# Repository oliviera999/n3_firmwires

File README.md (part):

# Firmwires – Projets ESP32 et Arduino (PlatformIO)

*Contexte : [salle aérée n³](https://n3.olution.info) · Données : [iot.olution.info](https://iot.olution.info). Voir [README racine](../README.md), [RECOMMANDATIONS_IOT](../RECOMMANDATIONS_IOT.md), [inventaire des appareils](../docs/inventaire_appareils.md).*

Dépôt regroupant **plusieurs firmwares** : deux projets principaux ESP32 (serre/aquaponie, station météo), trois projets ESP32-CAM d’envoi de photos vers un serveur web, et le kit **ratata** (ZYC0108-EN) avec exemples Arduino UNO et ESP32-CAM. Chaque projet (ou environnement) est compilable avec **PlatformIO**.

## Projets

| Projet | Dossier | Carte | Description |
|--------|---------|-------|-------------|
| **N3PhasmesProto (n3pp)** | `n3pp/` | ESP32 dev | Contrôle serre / aquaponie : température/humidité air, 4 capteurs humidité sol, pompe, luminosité, mails d’alerte, serveur web, NTP, OLED, deep sleep. |
| **MeteoStationPrototype (msp)** | `msp/` | ESP32 dev | Station météo + tracker solaire : 2× DHT, humidité sol, pluie, DS18B20, 4 LDR, 2 servos, relais, mail, serveur web, NTP, OLED. |
| **Upload Photos (unifié)** | `uploadphotosserver/` | ESP32-CAM | Un seul code, trois envs : **msp1** (msp1gallery, OTA distant HTTP, deep sleep 600 s, version courante `2.39`), **n3pp** (n3ppgallery, deep sleep 600 s, SD), **ffp3** (ffp3gallery, deep sleep 600 s). Upload et contrôle distant au réveil avec `X-Api-Key` (GET état outputs + POST version firmware, aligné serveur ≥ 5.0.306), retries de connexion, vérification du code HTTP retour. Tables `UploadPhoto*Outputs` (boards 5/6/7). Notifications mail SMTP (credentials partagés) : **une fois** au premier démarrage réel (hors réveil deep sleep, flag NVS `upcam/fb_mail`), démarrage/fin OTA, transitions matin/soir du créneau photo. `pio run -e msp1` / `-e n3pp` / `-e ffp3`. |
| **Upload Photos legacy** | `archive/uploadphotosserver_legacy/` | ESP32-CAM | Historique (`uploadphotosserver_*`) conservé en archive ; utiliser uniquement `uploadphotosserver/`. |
| **FFP5CS (aquaponie)** | `ffp5cs/` | ESP32 / ESP32-S3 | Contrôleur aquaponie (WROOM/S3), modulaire, API FFP3, réseau offline-first. Depuis v14.24, la sync distante WROOM utilise un document JSON dédié 2048 o pour absorber le payload `outputs/state` étendu (GPIO 118-123). Build WROOM plus complexe que n3pp/msp (pioarduino 2 passes) — voir [ffp5cs/docs/technical/COMPILATION_WROOM_PIOARDUINO_ET_ENVS.md](ffp5cs/docs/technical/COMPILATION_WROOM_PIOARDUINO_ET_ENVS.md). |
| **Poissonglouton (recyclage)** | `poissonglouton/` | ESP32-S3 | Compteur de bouteilles pour poubelle ludique : détection IR + ultrason (simple ou tandem), feedback audio I2S JC4827W543 (sortie speak), mode écran tactile ou headless, upload batch vers `/pgl/post-data`, heartbeat `/pgl/heartbeat` (flag `PGL_ENABLE_SERVER_HEARTBEAT`), deep sleep solaire. |
| **Banc énergie (INA226)** | `energie/` | ESP32-S3 | Banc d'essai des moniteurs de puissance INA226 du futur module d'aquaponie autonome (carte n3-universal) : panneau solaire / batterie plomb-AGM 12 V / consommation, mesure 1 Hz, POST 10 s vers `/energie-test/post-data` (famille serveur `energie`), SoC + alerte mail batterie basse, console série de calibration. Brique partagée `shared/n3_power`. Voir [energie/README.md](energie/README.md). |
| **LVGL_Widgets** | `à voir/LVGL_Widgets/` | ESP32-S3 | Interface écran tactile ; pas de serveur dédié. Dossier `à voir/` (prototype non maintenu en production). |
| **Ratata (ZYC0108-EN)** | `à voir/ratata/` | 7× UNO, 1× ESP32-CAM | Huit exemples : déplacement, servo, ultrason, évitement, suivi de ligne, voiture caméra WiFi. Dossier `à voir/`. |

## Prérequis

- [PlatformIO](https://platformio.org/) (CLI ou extension VSCode/Cursor) — **Core 6.1.19** (version épinglée en CI) :
  `pip install "platformio==6.1.19"`. PlatformIO **6.2.0** casse les builds ffp5cs WROOM pioarduino
  (`ModuleNotFoundError: SCons.Tool.FortranCommon` : tool-scons 4.8.1 remplacé par 4.11.1 en plein build).
- Selon le projet : carte **ESP32** (esp32dev), **ESP32-CAM** (esp32cam), ou **Arduino UNO** (uno)

## Compilation et upload

Chaque projet se compile et s’upload depuis **son dossier** :

```bash
# N3PhasmesProto (n3pp)
cd n3pp
pio run
pio run -t upload
pio device monitor

# MeteoStation (msp)
cd msp
pio run
pio run -t upload
pio device monitor

# Upload photos (ESP32-CAM unifié) – cible msp1, n3pp ou ffp3
cd uploadphotosserver
pio run -e msp1
pio run -e msp1 -t upload
pio device monitor -e msp1
# Ou : -e n3pp, -e ffp3 selon la galerie cible.

# Poissonglouton (ESP32-S3)
cd poissonglouton
pio run -e pgl-s3-headless
pio run -e pgl-s3-display
pio run -e pgl-s3-jc3248
pio run -e pgl-s3-headless -t upload

# Ratata – compiler un environnement (ex. 1_auto_move ou 6_1_esp32_car)
cd ratata
pio run -e 1_auto_move
pio run -e 1_auto_move -t upload
pio device monitor -e 1_auto_move
```

Adapter `upload_port` et `monitor_port` dans chaque `platformio.ini` (ex. `COM3`, `COM4`, `/dev/ttyUSB0`) selon ta machine.

## Build Windows : chemins courts, redirection et nettoyage

- **Redirection des artefacts** : les projets qui incluent `firmwires/scripts/pio_redirect_build_dir.py` (**ffp5cs**, **n3pp**, **msp**, **uploadphotosserver**, dossiers **test psram s3***) placent les binaires sous `C:\pio-builds\<slug-projet>\<env>\` sur Windows par défaut (évite chemins longs et soucis d’espaces dans le clone). **Linux / CI** : pas de redirection sauf si la variable d’environnement `N3_PIO_BUILD_ROOT` est définie — les artefacts restent alors sous `.pio/build/<env>/` (comportement GitHub Actions inchangé).
- **Désactiver la redirection** : `N3_PIO_BUILD_REDIRECT=0` (PowerShell : `$env:N3_PIO_BUILD_REDIRECT='0'`). **Autre racine** : `N3_PIO_BUILD_ROOT=D:\mes-builds`.
- **Chemins côté scripts** : `firmwires/scripts/Get-PioBuildHelpers.ps1` (fonctions `Get-N3PioFirmwareBin`, etc.) — utilisé par `IOT_n3/scripts/publish_ota.ps1` pour trouver `firmware.bin` / `littlefs.bin` que le build soit sous `C:\pio-builds` ou dans `.pio/build`.
- **Audit build (taille, duree, anomalies)** : `firmwires/scripts/Invoke-PioBuildAudit.ps1` pour mesurer les deltas avant/apres compilation (`BUILD_DIR`, `.pio/libdeps/<env>`, artefacts `firmware.bin`/`firmware.elf`), signaler les anomalies (taille, temps, chemins longs, espace disque) et ecrire un rapport texte.
- **Nettoyage global** : depuis la racine **IOT_n3**, `.\scripts\clean-firmware-builds.ps1` (ajouter `-WhatIf` pour simulation). Options : `-SyncPioBuilds` (purge aussi `C:\pio-builds\<slug>`), `-IncludeLegacyFfp5Mirror` pour `C:\ffp5cs_build`. **Alternance n3pp/ffp5cs** : ne pas nettoyer entre chaque build — utiliser `.\firmwires\scripts\Invoke-PioBuildFast.ps1`.
- **Cache compilation ffp5cs** : `build_cache_dir = C:/pio-builds/.pio-cache/ffp5cs` dans `ffp5cs/platformio.ini`.
- **S3 + espaces dans le chemin** : `ffp5cs/run_s3_build_from_safe_path.bat` (miroir sous `C:\pio-builds\ffp5cs-space-mirror` par défaut) ou `run_s3_fix_via_subst.bat` (lecteur `P:`).
- **Toolchain GCC 14 (Xtensa) + Arduino-ESP32 3.3.x** : erreur de link `undefined reference to __atomic_fetch_add_4` (libstdc++ / `shared_ptr` dans Network, FS, SD) — fichier `src/gcc_atomic_compat.c` dans **n3pp**, **msp** et **uploadphotosserver**. **ESP Mail Client** sur partition SPIFFS uniquement : script `firmwires/scripts/pio_patch_esp_mail_fs_spiffs.py` (référencé par **n3pp**, **msp** et **uploadphotosserver**), qui patche une fois `ESP_Mail_FS.h` dans `.pio/libdeps` (idempotent).

Les projets **legacy** caméra (`uploadphotosserver_*` hors dépôt unifié) ou exemples sans `platformio.ini` à la racine peuvent encore compiler uniquement sous `.pio/build/` : ajouter la même ligne `pre:../scripts/pio_redirect_build_dir.py` si besoin.

Exemple (depuis la racine `firmwires/`, build + audit sur `uploadphotosserver` env `msp1`) :

```powershell
.\scripts\Invoke-PioBuildAudit.ps1 `
  -ProjectRoot .\uploadphotosserver `
  -Environment msp1 `
  -PioArguments run,-e,msp1 `
  -MaxDurationSeconds 900 `
  -MaxBuildGrowthPercent 250
```

## Scripts de monitoring et erase-flash

### Référence FFP5CS (workflow complet)

Le projet **ffp5cs** définit le workflow de validation de référence, aligné sur les règles cœur de projet (offline-first, robustesse, vérification après modification) :

- **Workflow complet** : erase flash → flash firmware (+ LittleFS sauf prod) → monitoring N min → analyse du log. Script principal : `ffp5cs/erase_flash_fs_monitor_5min_analyze.ps1` (options `-Port`, `-Environment`, `-DurationMinutes`, `-SkipBuild`, `-NoPrompt`). Pour **ESP32-S3**, utiliser `-Environment wroom-s3-test` ou `-Environment wroom-s3-prod` ; scripts dédiés : `ffp5cs/run_s3_validation.ps1`, `ffp5cs/run_s3_psram_validation.ps1`, `ffp5cs/run_wroom_s3_prod_workflow.ps1`.
- **Monitoring** : `ffp5cs/monitor_5min.ps1` — capture série N secondes. Les logs et rapports d'analyse sont écrits dans le dossier dédié `ffp5cs/logs/` (plus à la racine du projet).
- **Monitoring crash/reboot** : `ffp5cs/monitor_until_crash.ps1` (wrapper PowerShell) appelle `ffp5cs/tools/monitor/monitor_until_crash.py` pour capturer jusqu'au crash/reboot, puis générer un rapport.
- **Analyse des logs** : `ffp5cs/analyze_log.ps1` (détaillée, spécifique FFP5CS/FFP3) et `ffp5cs/analyze_log_exhaustive.ps1` (crashes, WDT, heap, réseau, reboots). Rapport diagnostic : `ffp5cs/generate_diagnostic_report.ps1`. Toutes les sorties (fichiers .log, _analysis.txt, rapports .md) sont dans `ffp5cs/logs/`.

Pour tout travail sur **ffp5cs**, utiliser ces scripts depuis le dossier `ffp5cs/`. Voir aussi `ffp5cs/.cursor/rules/` et `ffp5cs/docs/INVENTAIRE_SCRIPTS_FFP5CS.md` pour l'inventaire des scripts.

- **Compilation de tous les envs** (évite les builds WROOM pioarduino en parallèle, qui peuvent corrompre le cache) : `ffp5cs/scripts/build_all_envs.ps1`.
- **Guide compilation FFP5CS WROOM** (pioarduino phase 2, secours `wroom-prod-pio6`, flash cohérent, vs n3pp/msp) : [ffp5cs/docs/technical/COMPILATION_WROOM_PIOARDUINO_ET_ENVS.md](ffp5cs/docs/technical/COMPILATION_WROOM_PIOARDUINO_ET_ENVS.md).
- **wroom-beta-local** (build, flash CP210x, tests Docker) : [ffp5cs/docs/technical/WROOM_BETA_LOCAL_BUILD_FLASH_TEST.md](ffp5cs/docs/technical/WROOM_BETA_LOCAL_BUILD_FLASH_TEST.md).
- **Compilation de tous les envs + beta-local** : `ffp5cs/scripts/build_all_envs.ps1 -IncludeBetaLocal`.
- **Build + upload + monitor beta-local** : `ffp5cs/build_upload_monitor_wroom_beta_local.ps1 -Port COM5` (raccourci COM4 : `build_upload_monitor_wroom_beta_local_com4.ps1`). Guide : [WROOM_BETA_LOCAL_BUILD_FLASH_TEST.md](ffp5cs/docs/technical/WROOM_BETA_LOCAL_BUILD_FLASH_TEST.md).
- **Tests unitaires natifs (Unity)** : `pio test -c platformio-native.ini -e native` depuis `ffp5cs/`, ou `ffp5cs/scripts/test_unit_all.ps1` (suites `test_config`, `test_nvs`, `test_server_url`).
- **Tests beta-local sur cible** : `ffp5cs/scripts/test_wroom_beta_local_serial.ps1` (upload + monitor + assertions logs).
- **Tests integration locale Docker + appareil** : `ffp5cs/scripts/test_wroom_beta_local_docker_integration.ps1` (stack docker, override URL LAN local, verification BDD).
- **Batterie de tests beta-local** : `ffp5cs/scripts/run_wroom_beta_local_test_suite.ps1` (secrets optionnels : copier `ffp5cs/scripts/.beta-local-test.env.example` vers `ffp5cs/scripts/.beta-local-test.env`).

### Scripts racine firmwires (multi-projets)

- `firmwires/scripts/analyze_log_generic.ps1` est **versionné** (Phase 5 audit 2026-05) : utilisable pour n3pp, msp, uploadphotosserver. Il prend `-LogFile <chemin>` et produit un rapport texte synthétique (crashes, WDT, heap, réseau).
- Les wrappers `firmwires/monitor_Nmin.ps1` et `firmwires/erase_flash_monitor.ps1` ne sont pas encore présents : utiliser `pio device monitor` / `pio run -t upload` depuis chaque dossier de firmware, ou s'inspirer du workflow ffp5cs.

| Emplacement | Rôle |
|-------------|------|
| `ffp5cs/scripts/Release-ComPort.ps1` | Libération du port COM (processus moniteur). |

**Exemples (référence ffp5cs, depuis `ffp5cs/`) :**

```powershell
# Workflow complet : erase, flash, LittleFS (sauf prod), monitor, analyse
.\erase_flash_fs_monitor_5min_analyze.ps1 -Environment wroom-test -Port COM4

# Monitoring seul
.\monitor_5min.ps1 -Port COM4
```

### Uploadphotosserver — build multi-env

Le firmware caméra unifié dispose d'un script de build multi-env : `uploadphotosserver/scripts/build_all_envs.ps1`.
Commandes directes possibles depuis `uploadphotosserver/` :

- `pio run -e msp1`
- `pio run -e n3pp`
- `pio run -e ffp3`
- **ESP32-CAM (uploadphotosserver)** : `pio run -e msp1` / `-e n3pp` / `-e ffp3` — **platformio/espressif32@6.13.0** + **`board = esp32cam`** (PSRAM + **HTTPS** par défaut depuis v2.54). Broches dans `uploadphotosserver/include/config.h`.
- **Monitoring 1–2 min** (série fiable sous Windows : DTR/RTS désactivés) : depuis `uploadphotosserver/`, `python tools/monitor_serial_cam.py COM5 -s 120` — fermer tout autre moniteur / outil sur le même COM ; dépendance : `pip install pyserial`.
- **Erase + flash + monitor** (camera) : `uploadphotosserver/scripts/erase_flash_monitor.ps1 -Environment msp1 -Port COM5 -DurationSeconds 300`.

## Stack ESP-IDF et plateforme

Tous les firmwares utilisent le **framework Arduino**. La chaîne de build est : plateforme → arduino-esp32 → ESP-IDF (sous-jacent).

**Versions arduino-ESP32 par type d'env :**
- **WROOM** (ffp5cs wroom-prod/test/beta, msp, n3pp) et **poissonglouton** (S3) : **arduino-esp32 3.3.7** (ESP-IDF 5.5.2) via la **plateforme pioarduino** ([pioarduino/platform-espressif32](https://github.com/pioarduino/platform-espressif32) release 55.03.37). Choix : stack IDF 5.x et alignement avec tous les firmwares WROOM du dépôt (uploadphotosserver, ESP32-CAM, reste en 6.13 : ci-dessous).
- **FFP5CS prod secours** : env **`wroom-prod-pio6`** = `espressif32@6.13.0` + Arduino **2.0.17** (build **1 passe**, sans pioarduino) si la phase 2 de `wroom-prod` échoue — détails et tutoriel : [COMPILATION_WROOM_PIOARDUINO_ET_ENVS.md](ffp5cs/docs/technical/COMPILATION_WROOM_PIOARDUINO_ET_ENVS.md).
- **uploadphotosserver** (ESP32-CAM) : envs **`msp1` / `n3pp` / `ffp3`** uniquement — **espressif32@6.13** + **`esp32cam`** + **HTTPS** (`USE_HTTPS_ENDPOINTS`) + diagnostic PSRAM au boot. Anciens envs `*-cam` et `msp1-https` supprimés (v2.54). Voir `uploadphotosserver/README.md` et `docs/HTTPS_MIGRATION.md`.
- **S3** (ffp5cs `wroom-s3-*`, y compris les envs PSRAM `wroom-s3-test-psram*` / `-devkit`, et **energie**) : **plateforme platformio/espressif32@6.13.0**, arduino-esp32 2.0.17 (bundlé, ESP-IDF 4.4.7). Alignement pioarduino possible à terme (erreur linker « gap » à résoudre).

Le **premier build** des projets WROOM télécharge la plateforme pioarduino (~500 Mo) ; en cas d'erreur de verrouillage de fichier (WinError 32/183), fermer les processus PlatformIO/IDE puis relancer.

### Recovery PlatformIO Windows (WROOM / esp32cam)

En cas d'erreur intermittente du type `TypeError: _path_exists ... NoneType` ou `FRAMEWORK_DIR None` :

1. Fermer Cursor/VSCode, tout moniteur série et tous les terminaux qui compilent/flashing.
2. Depuis `firmwires/`, lancer un build de warmup sur un firmware WROOM stable :
   - `cd n3pp`
   - `pio run -e esp32dev`
3. Revenir au firmware cible et relancer le build :
   - `cd ../uploadphotosserver`
   - `pio run -e msp1` (ou `-e n3pp`, `-e ffp3`)
4. Si l'erreur persiste : nettoyer le cache/framework PlatformIO local puis relancer la séquence warmup + build cible.
5. Sous Windows, éviter les builds parallèles pioarduino sur plusieurs projets en même temps.

Détails et APIs ESP-IDF utilisées en direct (ffp5cs) : [RECOMMANDATIONS_IOT.md § 2.9](../RECOMMANDATIONS_IOT.md#29-stack-esp-idf-et-conventions).

## Configuration des ports série

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
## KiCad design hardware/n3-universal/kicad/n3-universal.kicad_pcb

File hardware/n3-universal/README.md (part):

# n3-universal — étude de faisabilité (étape 0)

Projet : **une carte porteuse commune** aux trois systèmes (msp station météo,
n3pp serre/élevage, ffp5cs aquaponie), bi-module (site A1 WROOM DevKitC 38 broches /
site A2 ESP32-S3-DevKitC-1 — rev 0.2.3), 12/24 V, avec :
- rail capteurs commuté `+3V3_SW` (rev 0.2 : **LDO dédié U1 LD1117V33** derrière le
  P-FET Q7 IRF4905, **jumper bypass JP1 fermé par défaut** — ffp5cs, toujours alimenté,
  ne pilote pas le gate) et pont diviseur VBAT **permanent** (R38 + JP12 18k/100k — 22k jusqu'à la 0.2.1) ;
- bloc solaire TP4056 + 18650 en option de peuplement (msp/n3pp) ;
- RTC **DS3231** : VCC du module sur **`+3V3_SW`** (coupé en veille — PAS de rail
  permanent nécessaire) : le chip bascule nativement sur sa **pile bouton** et
  continue de compter (~3 µA, compensation température maintenue, CR2032 ≈ 8 ans) ;
  l'I2C est inaccessible sous VPF par conception (pas de fuite vers le rail éteint,
  pull-ups déjà sur `+3V3_SW`). Au réveil le firmware relit l'heure et resynchronise
  l'horloge interne (dérive deep sleep de l'ESP32 : minutes/jour → DS3231 ±2 ppm).
  Peuplement modules ZS-042 : **neutraliser le circuit de charge** (diode+200 Ω prévus
  LIR2032 — dessouder, monter une CR2032) et retirer la LED d'alim du module.
- slot **microSD unique** câblé aux deux sites : natif côté S3, et côté WROOM sur des
  nets inutilisés par msp/n3pp (CS=14/US3, CLK=23/AUX1, MOSI=25/AUX2, MISO=12 sans
  pull-up) — **msp et n3pp ont la SD sans rien sacrifier** ; seul ffp5cs-sur-WROOM
  arbitre par env de build (futur env `wroom-sd`, à créer au besoin : SD contre US_POTA+AUX), RTC **DS3231** et **3 INA226**
  sur I2C (INA alimentés par `+3V3_SW`) ;
- **rev 0.3 : plus de 230 V, plus de relais, plus d'étage transistor sur la carte.** Six borniers
  S / 5V / GND (J39-J44) commandent des **modules relais du commerce actifs à l'état haut** ; le
  profil 230 V s'alimente par un bloc 5 V externe (section « Rev 0.3 » ci-dessous,
  [`MODULES_RELAIS.md`](MODULES_RELAIS.md)). Jusqu'à la rev 0.2.3, le 230 V était sur la carte
  (PS1 Hi-Link + F1 + RV1 dans un coin isolé par des fentes) — → remplacé en rev 0.3. La carte
  `ffp5cs-wroom-prod-230v` reste gelée, comme les deux autres cartes dédiées.

> 🟢 **Rev 0.3.0 (2026-11-22) = version proposée à la commande** : carte **278 × 91 mm**, sans
> 230 V, sans relais, sans transistor de commande ; firmwares inchangés. Fichier :
> `exports/gerbers-n3-universal-v0.3.0.zip`. **Avant de payer** : essai sur table d'un module
> relais ([`MODULES_RELAIS.md`](MODULES_RELAIS.md) §8) et JLCDFM sur le nouveau zip
> ([`COMMANDE.md`](COMMANDE.md) §0). La 0.2.3 reste commandable (son zip est conservé) tant que la
> 0.3 n'est pas validée.
>
> 🟢 **Rev 0.2 (2026-10-07)** (→ remplacée par la 0.2.2 puis la 0.2.3) — régénérée de bout en bout (schéma,
> placement, routage, gerbers 2 oz) après la contre-vérification de la 0.1.2 (audit §13 :
> repères de sérigraphie décalés, J29/J30 sous le DevKit, Q7 NDP6020P introuvable). Ce qui
> change et pourquoi : tableau « 0.1.2 → 0.2 » ci-dessous ; contrôles : audit §14 ;
> dossier de fabrication : `exports/gerbers-n3-universal-v0.2.zip`.
>
> 📋 **Avant de commander** : lire **[`COMMANDE.md`](COMMANDE.md)** (options exactes du
> formulaire JLCPCB, devis du 2026-10-30, pourquoi pas de colis LCSC vers le Maroc, et procédure
> de devis PCB Maroc) et **[`AUDIT-2026-08-28.md`](AUDIT-2026-08-28.md)** (contre-vérification
> pré-commande : verdict, constats retenus, check-list rev 0.2). Fichiers d'assemblage
> éventuel : [`exports/pcba/`](exports/pcba/).
>
> 🟢 **Rev 0.2.3 (2026-10-31) = version à commander** (→ remplacée en rev 0.3, zip conservé) : site A1 en **ESP32 DevKitC 38 broches**,
> rangées droites d'A1 et A2 doublées 25,4 / 22,86 mm, carte reroutée (section « Rev 0.2.3 »
> ci-dessous). Fichier : `exports/gerbers-n3-universal-v0.2.3.zip` ; le zip 0.2.2 est périmé.
>
> 🔶 **Cuivre 1 oz depuis le 2026-10-30** (ex-2 oz, −58 $ sur 10 cartes) : les charges réelles
> (pompes, chauffage d'aquarium ≤ 300 W) sont loin de la limite des pistes contacts 2,5 mm en
> 1 oz (≈ 4,5 A à +10 °C). Règle d'usage : **≤ 1 kW résistif / 3 A moteur par canal**
> (`COMMANDE.md` §1 et §5). Empilage 1 oz porté par le `gbrjob` du zip. Résultats JLCDFM
> (v0.2.3) et lignes attendues dans `COMMANDE.md` §0.
>
> ⏸️ **Avant de commander (2026-11-18)** (→ arbitré le 2026-11-19, réalisé en rev 0.3 : sans
> l'étage à transistor non plus, voir `SIMPLIFICATION_PROPOSEE.md` §11) : une simplification est à l'étude —
> [`SIMPLIFICATION_PROPOSEE.md`](SIMPLIFICATION_PROPOSEE.md) : sortir de la carte l'alimentation
> 230 V et les relais (module relais du commerce piloté par l'étage à transistor conservé),
> carte ≈ 278 × 90 mm, plus aucun 230 V sur le PCB. **Proposition en attente d'arbitrage** : rien
> n'est modifié, la 0.2.3 reste la seule version commandable. Le header **J38** de la 0.2.3 permet
> déjà de piloter un module relais externe actif à l'état bas (collecteurs + GND + 5 V).
> Prompt de lancement du chantier : [`PROMPT_REV_0.3.md`](PROMPT_REV_0.3.md).
>
> 🧭 [`EVOLUTIONS_PROPOSEES.md`](EVOLUTIONS_PROPOSEES.md) : l'étude du sélecteur AUTO / ON,
> du retour d'état et de la connectique — **décisions actées le 2026-10-06 et appliquées
> en 0.2** (encadré en tête du document).
>
> ⛔ **Rev 0.2.2 (2026-10-17) — NE PAS COMMANDER la 0.2** : la simulation SPICE
> ([`simulation/SIMULATION.md`](simulation/SIMULATION.md)) a montré que **Q7 (IRF4905, rail
> capteurs) était câblé à l'envers** (drain sur +5V, source sur LDO_IN : la diode interne
> alimente le LDO en permanence, le rail ne se coupe jamais sur les profils msp/n3pp).
> Corrigé dans `generate.py` (source = +5V, drain = LDO_IN), schéma + BOM régénérés, garde
> `tools/check_fet_orientation.py`, champs `Sim.*` (schéma simulable dans KiCad). **Le PCB
> routé n'est pas encore à jour** : voir « Rev 0.2.1 » ci-dessous.

## Rev 0.3 — sans 230 V, sans relais, sans étage transistor (2026-11-22) : carte reroutée

Arbitrages du 2026-11-19 ([`SIMPLIFICATION_PROPOSEE.md`](SIMPLIFICATION_PROPOSEE.md) §11) :
l'alimentation 230 V, les six relais et leur étage de commande quittent la carte. **Firmwares
inchangés** : même GPIO, même sens (broche haute = relais collé) ; `pinmap_universel_propose.json`
n'est pas modifié. Mode d'emploi, câblage par profil et essai sur table :
[`MODULES_RELAIS.md`](MODULES_RELAIS.md).

| Changement | Pourquoi | Conséquence d'usage |
|---|---|---|
| **Bloc 230 V retiré** : PS1, F1, RV1, J27, H5, pistes secteur, 19 fentes, règles `Mains`, zone d'exclusion du plan GND, vis nylon | plus aucun 230 V sur le circuit imprimé | ffp5cs 230 V s'alimente par un **bloc 5 V ≥ 2 A** sur J2 ou J1 ; le 230 V ne touche que les modules relais |
| **Relais K1-K6 et borniers de charge J3-J6, J23, J24 retirés** ; header J38 retiré | relais du commerce, remplaçables, hors carte | modules **actifs à l'état haut** (type KY-019) |
| **Étage transistor retiré** (Q1-Q6, diodes D1-D4/D6/D7, LED1-4/6/7 et leurs résistances) | le module porte déjà transistor, diode et LED | commande directe : GPIO → **Rs 470 Ω** (R1-R4, R28, R31) → borne S ; rappel **10 kΩ** (R5-R8, R29, R32) |
| **Six borniers 3 points 5,08 mm J39-J44 : S / 5V / GND**, un par canal, en bord haut | trois fils par module, sans répartiteur | sérigraphie « S 5V GND » au-dessus de chaque bornier |
| **JP5-JP10 reliés directement** : broche 1 = +3V3 (ON), 2 = ligne, 3 = GND (OFF) | plus de résistance de forçage à prévoir : Rs limite le courant | sans cavalier = AUTO ; **JP7 (chauffage) et JP10 (GPIO45 du S3) sans position ON** |
| **D5 = 1N5822 sur toutes les cartes** + **JP22** (2 broches, « USB SEUL ») en parallèle | l'USB du DevKit et la source de la carte peuvent coexister | **source à 5,2 V, JP22 ôté** ; n3pp sur chargeur 5,0 V : JP22 posé, jamais d'USB en même temps |
| **C14 220 µF sur VIN_5V** (derrière D5) | tient le DevKit pendant le creux de fermeture de Q7 (SIMULATION §13.4) | posé sur toutes les cartes |
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
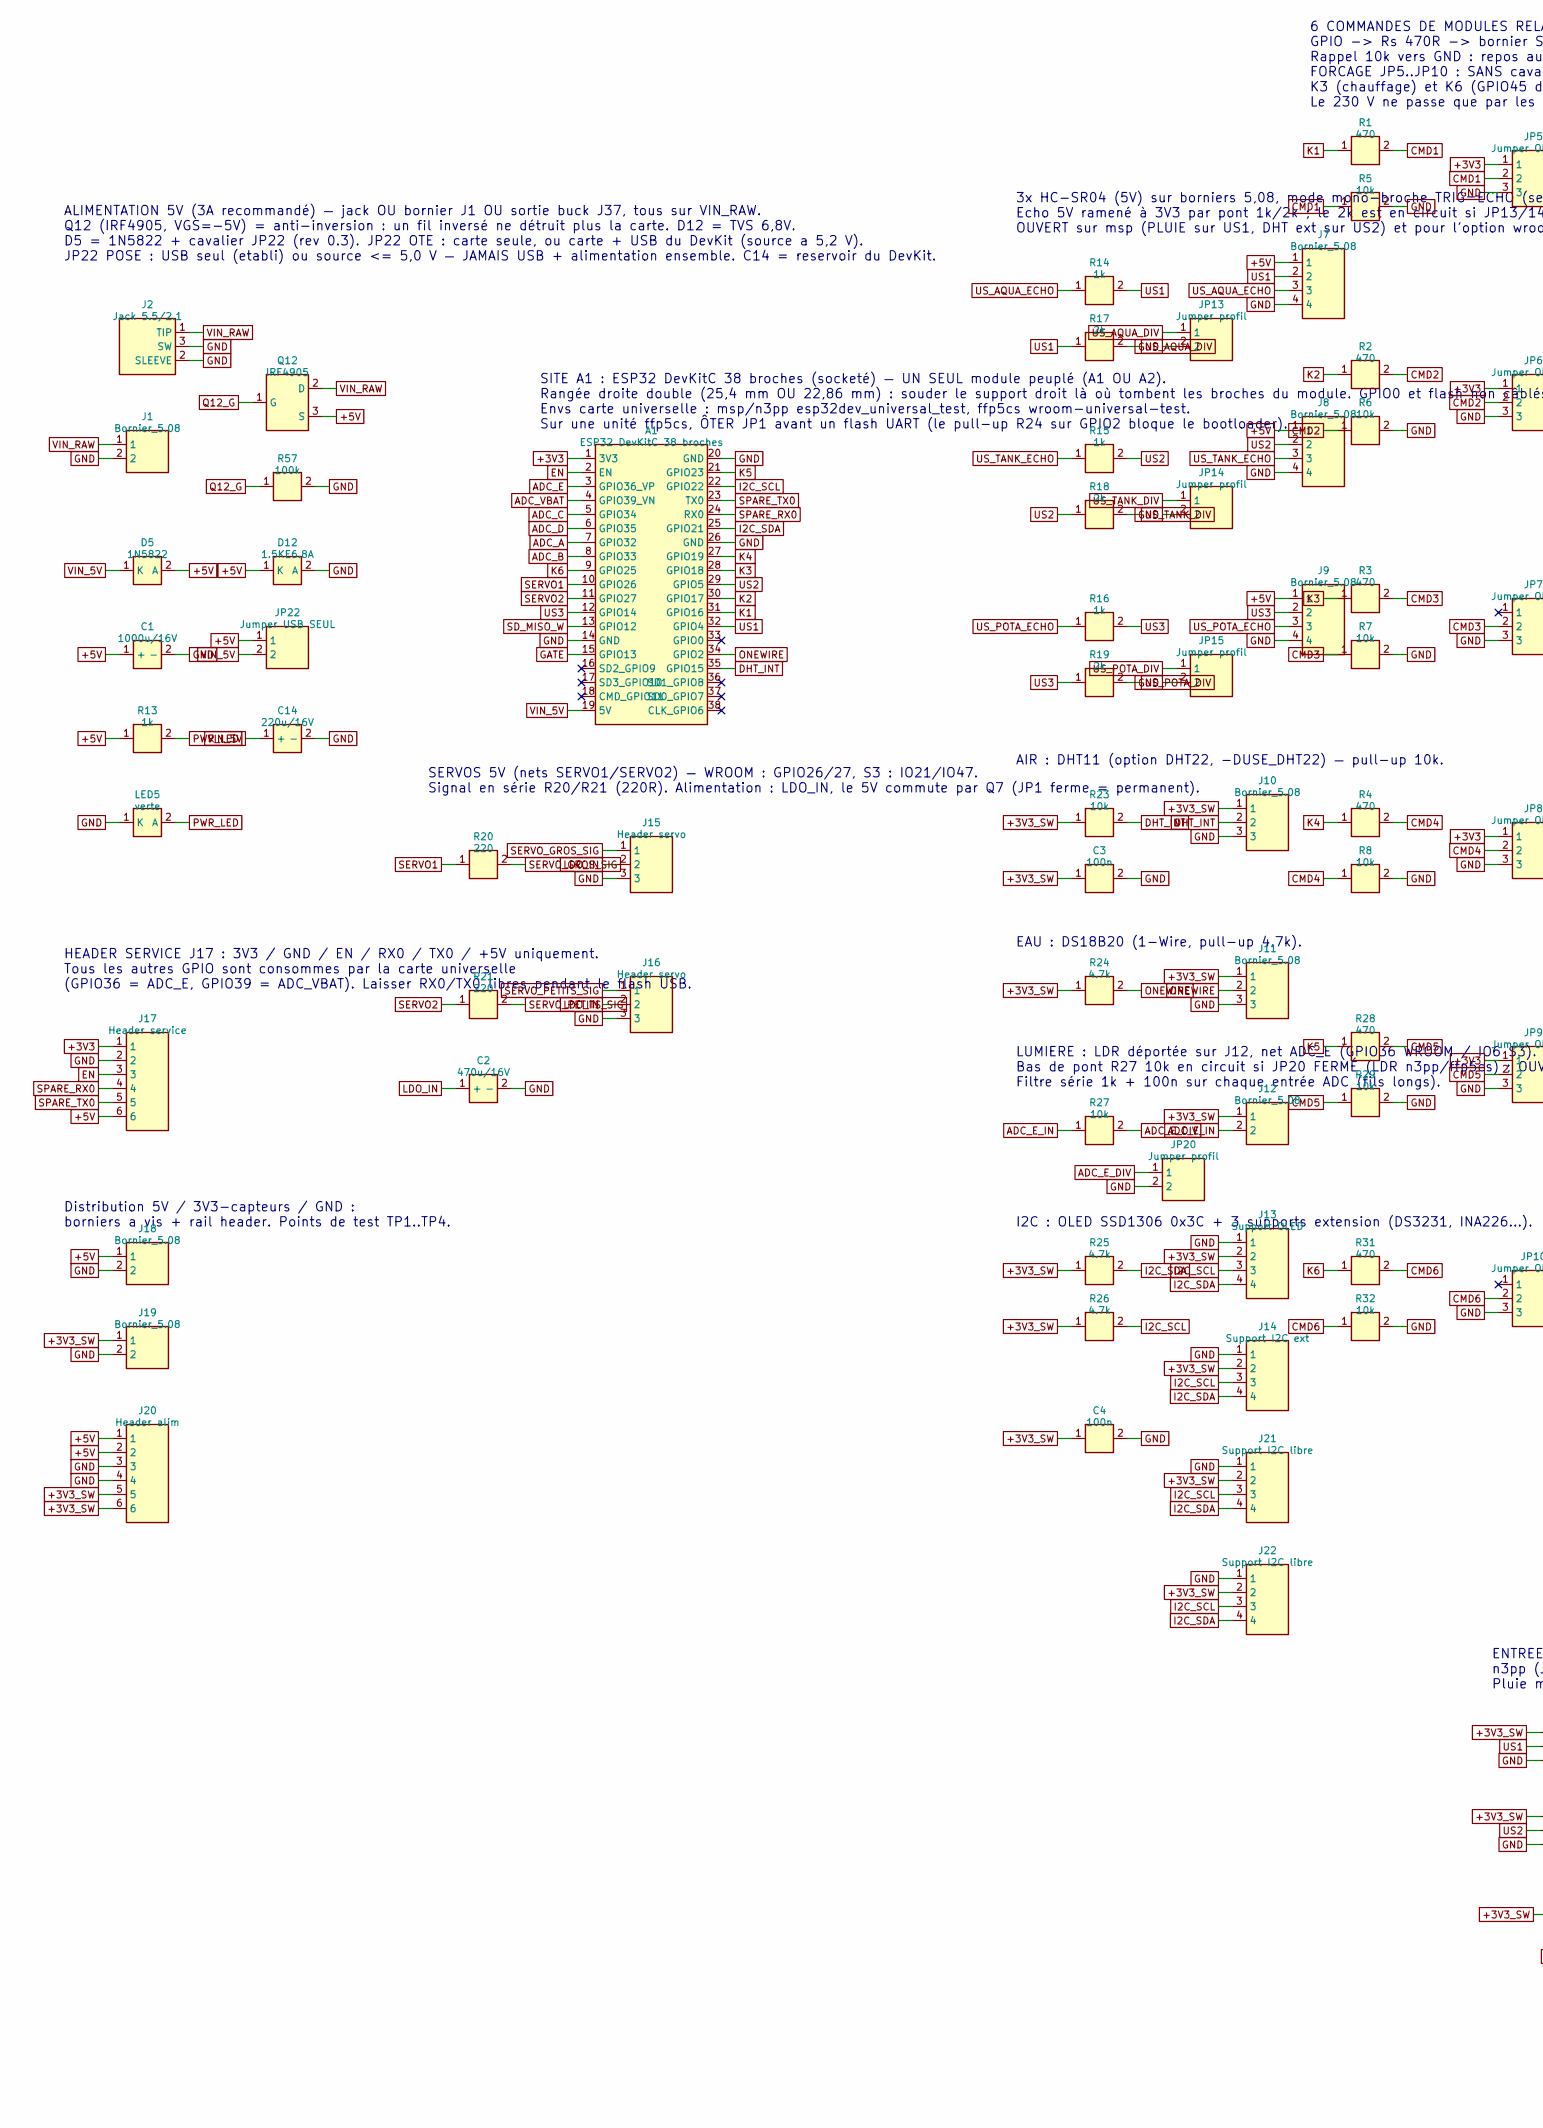
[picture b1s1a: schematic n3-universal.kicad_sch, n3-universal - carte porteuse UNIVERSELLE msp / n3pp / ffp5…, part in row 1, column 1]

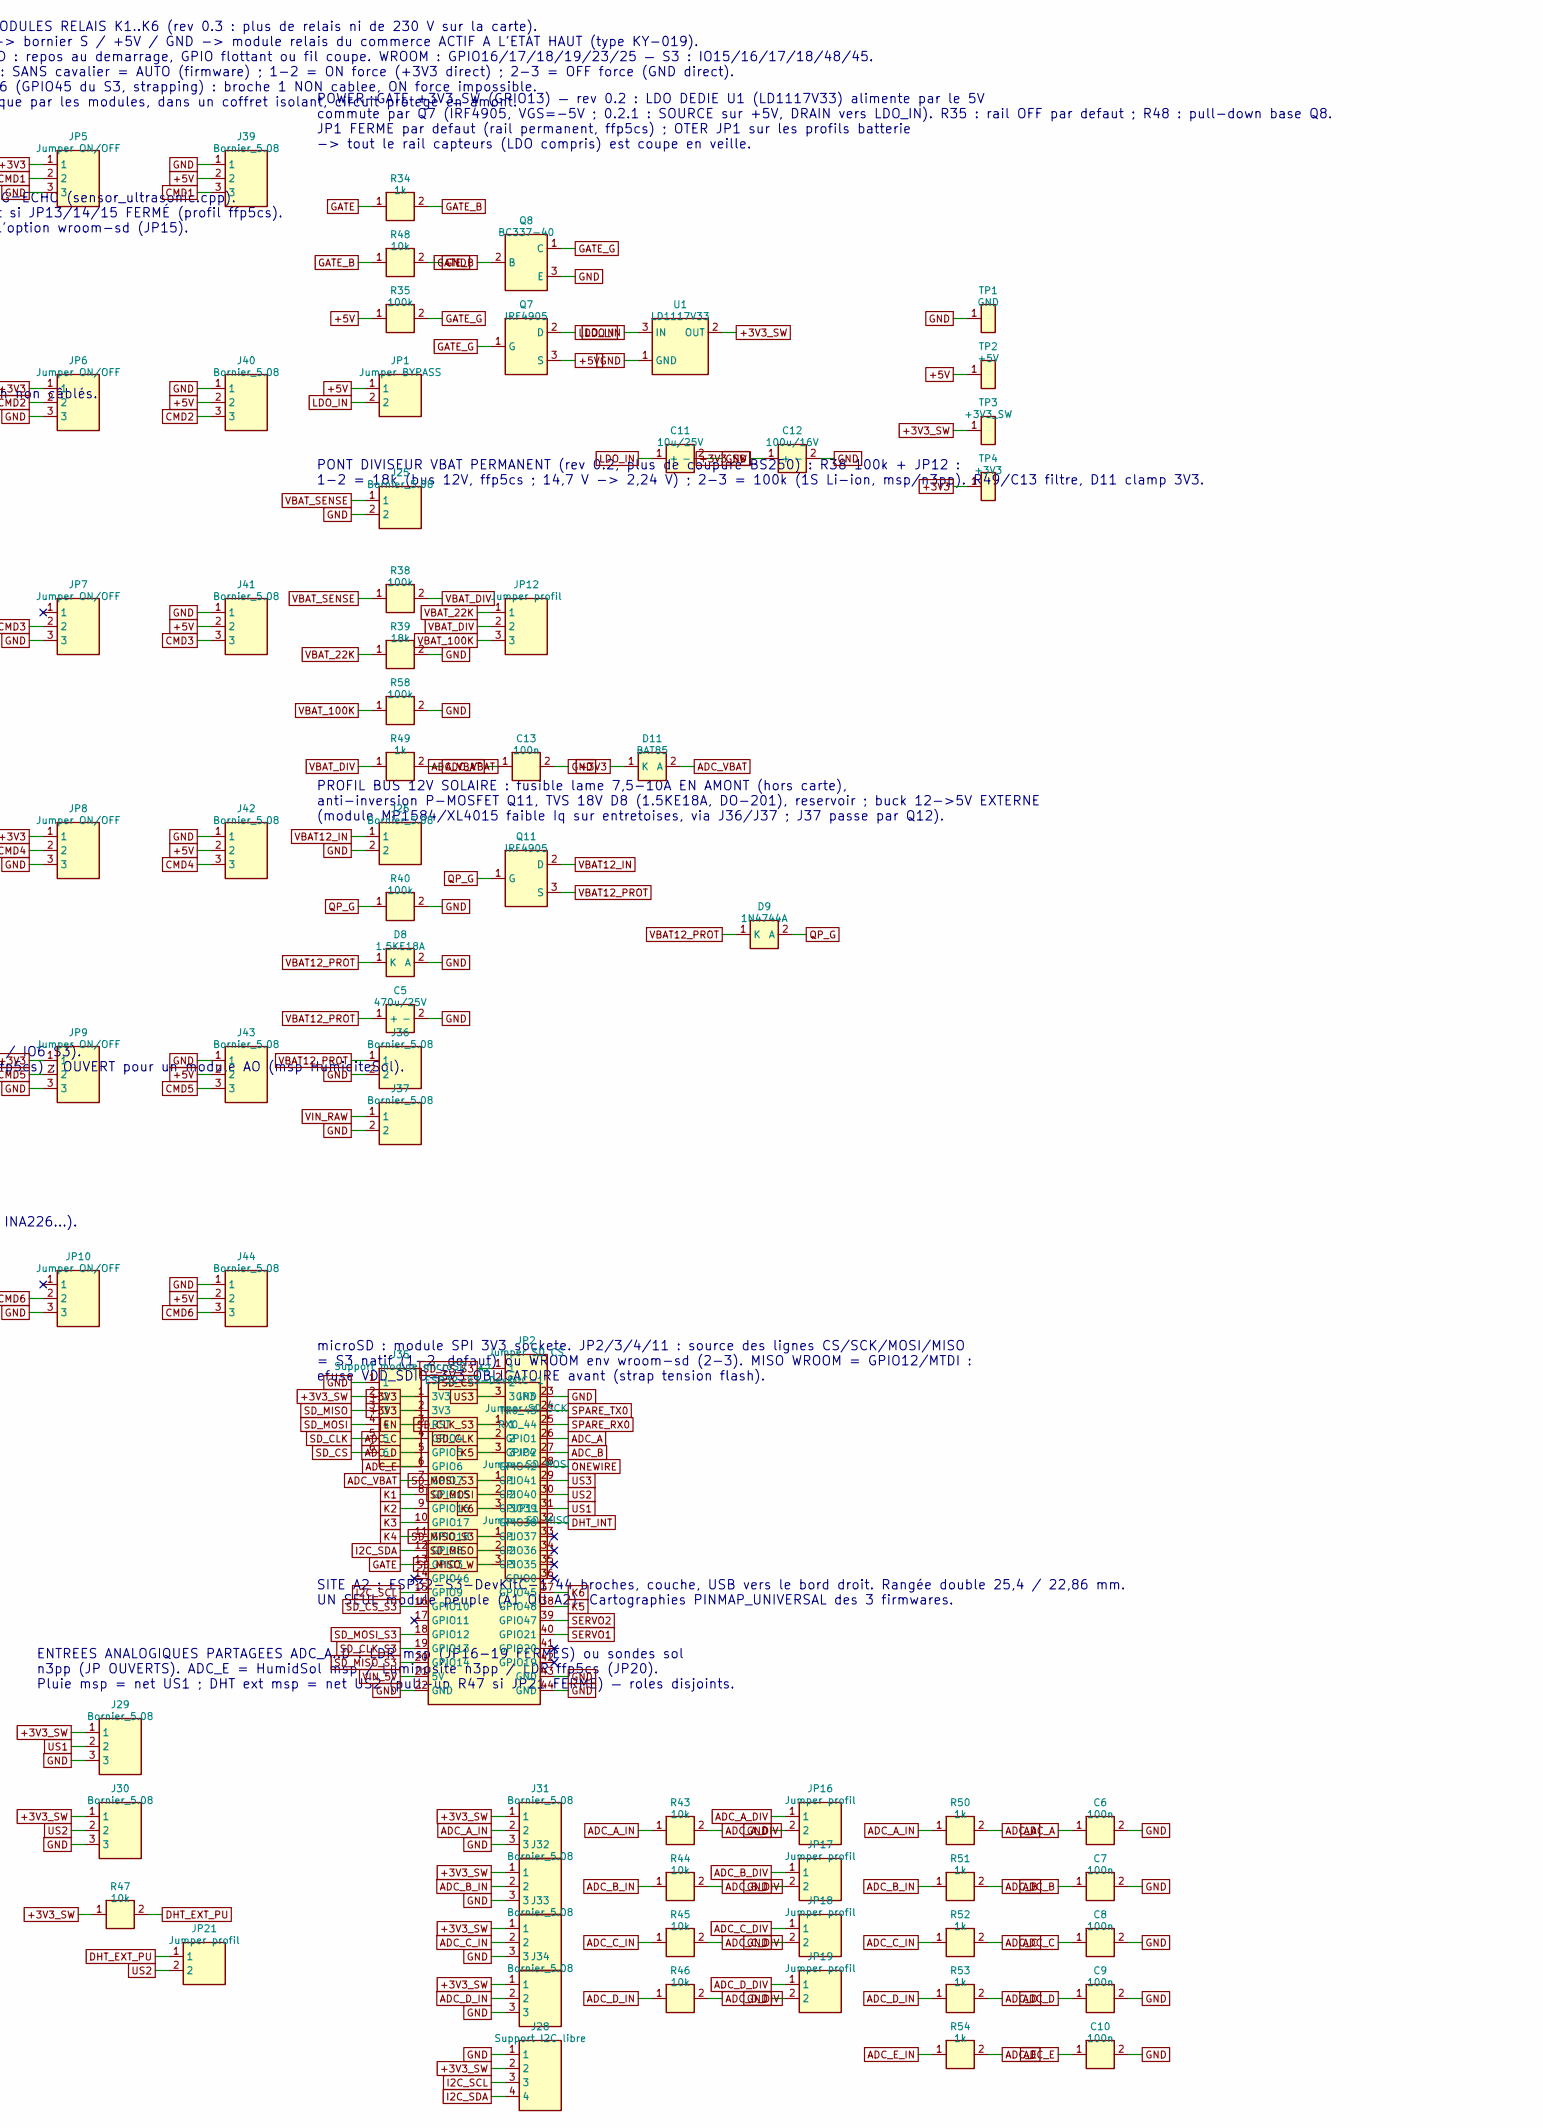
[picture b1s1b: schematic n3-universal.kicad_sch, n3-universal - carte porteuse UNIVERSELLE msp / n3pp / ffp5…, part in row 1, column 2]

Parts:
A1: ESP32 DevKitC 38 broches; ESP32_DevKitC_38pin
A2: ESP32-S3-DevKitC-1; ESP32_S3_DevKitC_1_44pin
C1: 1000u/16V; CP_Radial_D10.0mm_P5.00mm
C2: 470u/16V; CP_Radial_D8.0mm_P3.50mm
C3, C4, C6, C7, C8, C9, C10, C13: 100n; C_Disc_D5.0mm_W2.5mm_P5.00mm
C5: 470u/25V; CP_Radial_D10.0mm_P5.00mm
C11: 10u/25V; CP_Radial_D5.0mm_P2.50mm
C12: 100u/16V; CP_Radial_D6.3mm_P2.50mm
C14: 220u/16V; CP_Radial_D8.0mm_P3.50mm
D5: 1N5822; D_DO-201AD_P15.24mm_Horizontal
D8: 1.5KE18A; D_DO-201AD_P15.24mm_Horizontal
D9: 1N4744A; D_DO-41_SOD81_P5.08mm_Vertical_AnodeUp
D11: BAT85; D_DO-35_SOD-123_Dual_P7.62mm
D12: 1.5KE6.8A; D_DO-201AD_P15.24mm_Horizontal
J1, J12, J18, J19, J25, J26, J36, J37: Bornier_5.08; TerminalBlock_bornier-2_P5.08mm
J2: Jack 5.5/2.1; BarrelJack_Horizontal
J7, J8, J9: Bornier_5.08; TerminalBlock_bornier-4_P5.08mm
J10, J11, J29, J30, J31, J32, J33, J34, J39, J40, J41, J42, J43, J44: Bornier_5.08; TerminalBlock_bornier-3_P5.08mm
J13: Support OLED; PinSocket_1x04_P2.54mm_Vertical
J14: Support I2C ext; PinSocket_1x04_P2.54mm_Vertical
J15, J16: Header servo; PinHeader_1x03_P2.54mm_Vertical
J17: Header service; PinHeader_1x06_P2.54mm_Vertical
J20: Header alim; PinHeader_1x06_P2.54mm_Vertical
J21, J22, J28: Support I2C libre; PinSocket_1x04_P2.54mm_Vertical
J35: Support module microSD; PinSocket_1x06_P2.54mm_Vertical
JP1: Jumper BYPASS; PinHeader_1x03_P2.54mm_Vertical
JP2: Jumper SD CS; PinHeader_1x03_P2.54mm_Vertical
JP3: Jumper SD SCK; PinHeader_1x03_P2.54mm_Vertical
JP4: Jumper SD MOSI; PinHeader_1x03_P2.54mm_Vertical
JP5, JP6, JP7, JP8, JP9, JP10: Jumper ON/OFF; PinHeader_1x03_P2.54mm_Vertical
JP11: Jumper SD MISO; PinHeader_1x03_P2.54mm_Vertical
JP12: Jumper profil; PinHeader_1x03_P2.54mm_Vertical
JP13, JP14, JP15, JP16, JP17, JP18, JP19, JP20, JP21: Jumper profil; PinHeader_1x02_P2.54mm_Vertical
JP22: Jumper USB SEUL; PinHeader_1x02_P2.54mm_Vertical
LED5: verte; LED_D5.0mm
Q7, Q11, Q12: IRF4905; TO-220-3_Vertical_GDS
Q8: BC337-40; TO-92_Inline_Wide_CBE
R1, R2, R3, R4, R28, R31: 470; R_Axial_DIN0207_L6.3mm_D2.5mm_P10.16mm_Horizontal
R5, R6, R7, R8, R23, R27, R29, R32, R43, R44, R45, R46, R47, R48: 10k; R_Axial_DIN0207_L6.3mm_D2.5mm_P10.16mm_Horizontal
R13, R14, R15, R16, R34, R49, R50, R51, R52, R53, R54: 1k; R_Axial_DIN0207_L6.3mm_D2.5mm_P10.16mm_Horizontal
R17, R18, R19: 2k; R_Axial_DIN0207_L6.3mm_D2.5mm_P10.16mm_Horizontal
R20, R21: 220; R_Axial_DIN0207_L6.3mm_D2.5mm_P10.16mm_Horizontal
R24, R25, R26: 4.7k; R_Axial_DIN0207_L6.3mm_D2.5mm_P10.16mm_Horizontal
R35, R38, R40, R57, R58: 100k; R_Axial_DIN0207_L6.3mm_D2.5mm_P10.16mm_Horizontal
R39: 18k; R_Axial_DIN0207_L6.3mm_D2.5mm_P10.16mm_Horizontal
TP1: GND; TestPoint_THTPad_D2.0mm_Drill1.0mm
TP2: +5V; TestPoint_THTPad_D2.0mm_Drill1.0mm
TP3: +3V3_SW; TestPoint_THTPad_D2.0mm_Drill1.0mm
TP4: +3V3; TestPoint_THTPad_D2.0mm_Drill1.0mm
U1: LD1117V33; TO-220-3_Vertical_LDO

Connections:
+3V3: A1.1 (3V3), A2.1 (3V3), A2.2 (3V3), D11.1 (K), J17.1, JP5.1, JP6.1, JP8.1, JP9.1, TP4.1
+3V3_SW: C3.1, C4.1, C12.1 (+), J10.1, J11.1, J12.1, J13.2, J14.2, J19.1, J20.5, J20.6, J21.2, J22.2, J28.2, J29.1, J30.1, J31.1, J32.1, J33.1, J34.1, J35.2, R23.1, R24.1, R25.1, R26.1, R47.1, TP3.1, U1.2 (OUT)
+5V: C1.1 (+), D5.2 (A), D12.1 (K), J7.1, J8.1, J9.1, J17.6, J18.1, J20.1, J20.2, J39.2, J40.2, J41.2, J42.2, J43.2, J44.2, JP1.1, JP22.1, Q7.3 (S), Q12.3 (S), R13.1, R35.1, TP2.1
ADC_A: A1.7 (GPIO32), A2.26 (GPIO1), C6.1, R50.2
ADC_A_DIV: JP16.1, R43.2
ADC_A_IN: J31.2, R43.1, R50.1
ADC_B: A1.8 (GPIO33), A2.27 (GPIO2), C7.1, R51.2
ADC_B_DIV: JP17.1, R44.2
ADC_B_IN: J32.2, R44.1, R51.1
ADC_C: A1.5 (GPIO34), A2.4 (GPIO4), C8.1, R52.2
ADC_C_DIV: JP18.1, R45.2
ADC_C_IN: J33.2, R45.1, R52.1
ADC_D: A1.6 (GPIO35), A2.5 (GPIO5), C9.1, R53.2
ADC_D_DIV: JP19.1, R46.2
ADC_D_IN: J34.2, R46.1, R53.1
ADC_E: A1.3 (GPIO36_VP), A2.6 (GPIO6), C10.1, R54.2
ADC_E_DIV: JP20.1, R27.2
ADC_E_IN: J12.2, R27.1, R54.1
ADC_VBAT: A1.4 (GPIO39_VN), A2.7 (GPIO7), C13.1, D11.2 (A), R49.2
CMD1: J39.3, JP5.2, R1.2, R5.1
CMD2: J40.3, JP6.2, R2.2, R6.1
CMD3: J41.3, JP7.2, R3.2, R7.1
CMD4: J42.3, JP8.2, R4.2, R8.1
CMD5: J43.3, JP9.2, R28.2, R29.1
CMD6: J44.3, JP10.2, R31.2, R32.1
DHT_EXT_PU: JP21.1, R47.2
DHT_INT: A1.35 (GPIO15), A2.32 (GPIO38), J10.2, R23.2
EN: A1.2 (EN), A2.3 (RST), J17.3
GATE: A1.15 (GPIO13), A2.13 (GPIO3), R34.1
GATE_B: Q8.2 (B), R34.2, R48.1
GATE_G: Q7.1 (G), Q8.1 (C), R35.2
GND: A1.14 (GND), A1.20 (GND), A1.26 (GND), A2.22 (GND), A2.23 (GND), A2.43 (GND), A2.44 (GND), C1.2 (-), C2.2 (-), C3.2, C4.2, C5.2 (-), C6.2, C7.2, C8.2, C9.2, C10.2, C11.2 (-), C12.2 (-), C13.2, C14.2 (-), D8.2 (A), D12.2 (A), J1.2, J2.2 (SLEEVE), J2.3 (SW), J7.4, J8.4, J9.4, J10.3, J11.3, J13.1, J14.1, J15.3, J16.3, J17.2, J18.2, J19.2, J20.3, J20.4, J21.1, J22.1, J25.2, J26.2, J28.1, J29.3, J30.3, J31.3, J32.3, J33.3, J34.3, J35.1, J36.2, J37.2, J39.1, J40.1, J41.1, J42.1, J43.1, J44.1, JP5.3, JP6.3, JP7.3, JP8.3, JP9.3, JP10.3, JP13.2, JP14.2, JP15.2, JP16.2, JP17.2, JP18.2, JP19.2, JP20.2, LED5.1 (K), Q8.3 (E), R5.2, R6.2, R7.2, R8.2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
I2C_SCL: A1.22 (GPIO22), A2.15 (GPIO9), J13.3, J14.3, J21.3, J22.3, J28.3, R26.2
I2C_SDA: A1.25 (GPIO21), A2.12 (GPIO8), J13.4, J14.4, J21.4, J22.4, J28.4, R25.2
K1: A1.31 (GPIO16), A2.8 (GPIO15), R1.1
K2: A1.30 (GPIO17), A2.9 (GPIO16), R2.1
K3: A1.28 (GPIO18), A2.10 (GPIO17), R3.1
K4: A1.27 (GPIO19), A2.11 (GPIO18), R4.1
K5: A1.21 (GPIO23), A2.38 (GPIO48), JP3.3, R28.1
K6: A1.9 (GPIO25), A2.37 (GPIO45), JP4.3, R31.1
LDO_IN: C2.1 (+), C11.1 (+), J15.2, J16.2, JP1.2, Q7.2 (D), U1.3 (IN)
ONEWIRE: A1.34 (GPIO2), A2.28 (GPIO42), J11.2, R24.2
PWR_LED: LED5.2 (A), R13.2
Q12_G: Q12.1 (G), R57.1
QP_G: D9.2 (A), Q11.1 (G), R40.1
SD_CLK: J35.5, JP3.2
SD_CLK_S3: A2.19 (GPIO13), JP3.1
SD_CS: J35.6, JP2.2
SD_CS_S3: A2.16 (GPIO10), JP2.1
SD_MISO: J35.3, JP11.2
SD_MISO_S3: A2.20 (GPIO14), JP11.1
SD_MISO_W: A1.13 (GPIO12), JP11.3
SD_MOSI: J35.4, JP4.2
SD_MOSI_S3: A2.18 (GPIO12), JP4.1
SERVO1: A1.10 (GPIO26), A2.40 (GPIO21), R20.1
SERVO2: A1.11 (GPIO27), A2.39 (GPIO47), R21.1
SERVO_GROS_SIG: J15.1, R20.2
SERVO_PETITS_SIG: J16.1, R21.2
SPARE_RX0: A1.24 (RX0), A2.25 (RX0_44), J17.4
SPARE_TX0: A1.23 (TX0), A2.24 (TX0_43), J17.5
US1: A1.32 (GPIO4), A2.31 (GPIO39), J7.2, J29.2, R14.2, R17.1
US2: A1.29 (GPIO5), A2.30 (GPIO40), J8.2, J30.2, JP21.2, R15.2, R18.1
US3: A1.12 (GPIO14), A2.29 (GPIO41), J9.2, JP2.3, R16.2, R19.1
US_AQUA_DIV: JP13.1, R17.2
US_AQUA_ECHO: J7.3, R14.1
US_POTA_DIV: JP15.1, R19.2
US_POTA_ECHO: J9.3, R16.1
US_TANK_DIV: JP14.1, R18.2
US_TANK_ECHO: J8.3, R15.1
VBAT12_IN: J26.1, Q11.2 (D)
VBAT12_PROT: C5.1 (+), D8.1 (K), D9.1 (K), J36.1, Q11.3 (S)
VBAT_22K: JP12.1, R39.1
VBAT_100K: JP12.3, R58.1
VBAT_DIV: JP12.2, R38.2, R49.1
VBAT_SENSE: J25.1, R38.1
VIN_5V: A1.19 (5V), A2.21 (5V), C14.1 (+), D5.1 (K), JP22.2
VIN_RAW: J1.1, J2.1 (TIP), J37.1, Q12.2 (D)

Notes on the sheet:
ALIMENTATION 5V (3A recommandé) — jack OU bornier J1 OU sortie buck J37, tous sur VIN_RAW. Q12 (IRF4905, VGS=-5V) = anti-inversion : un fil inversé ne détruit plus la carte. D12 = TVS 6,8V. D5 = 1N5822 + cavalier JP22 (rev 0.3). JP22 OTE : carte seule, ou carte + USB du DevKit (source a 5,2 V). JP2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
SITE A1 : ESP32 DevKitC 38 broches (socketé) — UN SEUL module peuplé (A1 OU A2). Rangée droite double (25,4 mm OU 22,86 mm) : souder le support droit là où tombent les broches du module. GPIO0 et flash non câblés. Envs carte universelle : msp/n3pp esp32dev_universal_test, ffp5cs wroom-universal-tes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
SERVOS 5V (nets SERVO1/SERVO2) — WROOM : GPIO26/27, S3 : IO21/IO47. Signal en série R20/R21 (220R). Alimentation : LDO_IN, le 5V commute par Q7 (JP1 ferme = permanent).
3x HC-SR04 (5V) sur borniers 5,08, mode mono-broche TRIG=ECHO (sensor_ultrasonic.cpp). Echo 5V ramené à 3V3 par pont 1k/2k ; le 2k est en circuit si JP13/14/15 FERMÉ (profil ffp5cs). OUVERT sur msp (PLUIE sur US1, DHT ext sur US2) et pour l'option wroom-sd (JP15).
AIR : DHT11 (option DHT22, -DUSE_DHT22) — pull-up 10k.
EAU : DS18B20 (1-Wire, pull-up 4.7k).
LUMIERE : LDR déportée sur J12, net ADC_E (GPIO36 WROOM / IO6 S3). Bas de pont R27 10k en circuit si JP20 FERMÉ (LDR n3pp/ffp5cs) ; OUVERT pour un module AO (msp HumiditeSol). Filtre série 1k + 100n sur chaque entrée ADC (fils longs).
I2C : OLED SSD1306 0x3C + 3 supports extension (DS3231, INA226...).
6 COMMANDES DE MODULES RELAIS K1..K6 (rev 0.3 : plus de relais ni de 230 V sur la carte). GPIO -> Rs 470R -> bornier S / +5V / GND -> module relais du commerce ACTIF A L'ETAT HAUT (type KY-019). Rappel 10k vers GND : repos au demarrage, GPIO flottant ou fil coupe. WROOM : GPIO16/17/18/19/23/25 — S3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
HEADER SERVICE J17 : 3V3 / GND / EN / RX0 / TX0 / +5V uniquement. Tous les autres GPIO sont consommes par la carte universelle (GPIO36 = ADC_E, GPIO39 = ADC_VBAT). Laisser RX0/TX0 libres pendant le flash USB.
Distribution 5V / 3V3-capteurs / GND : borniers a vis + rail header. Points de test TP1..TP4.
POWER-GATE +3V3_SW (GPIO13) — rev 0.2 : LDO DEDIE U1 (LD1117V33) alimente par le 5V commute par Q7 (IRF4905, VGS=-5V ; 0.2.1 : SOURCE sur +5V, DRAIN vers LDO_IN). R35 : rail OFF par defaut ; R48 : pull-down base Q8. JP1 FERME par defaut (rail permanent, ffp5cs) ; OTER JP1 sur les profils batterie -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
PONT DIVISEUR VBAT PERMANENT (rev 0.2, plus de coupure BS250) : R38 100k + JP12 : 1-2 = 18k (bus 12V, ffp5cs ; 14,7 V -> 2,24 V) ; 2-3 = 100k (1S Li-ion, msp/n3pp). R49/C13 filtre, D11 clamp 3V3.
PROFIL BUS 12V SOLAIRE : fusible lame 7,5-10A EN AMONT (hors carte), anti-inversion P-MOSFET Q11, TVS 18V D8 (1.5KE18A, DO-201), reservoir ; buck 12->5V EXTERNE (module MP1584/XL4015 faible Iq sur entretoises, via J36/J37 ; J37 passe par Q12).
microSD : module SPI 3V3 sockete. JP2/3/4/11 : source des lignes CS/SCK/MOSI/MISO = S3 natif (1-2, defaut) ou WROOM env wroom-sd (2-3). MISO WROOM = GPIO12/MTDI : efuse VDD_SDIO=3V3 OBLIGATOIRE avant (strap tension flash).
SITE A2 : ESP32-S3-DevKitC-1 44 broches, couche, USB vers le bord droit. Rangée double 25,4 / 22,86 mm. UN SEUL module peuple (A1 OU A2). Cartographies PINMAP_UNIVERSAL des 3 firmwares.
ENTREES ANALOGIQUES PARTAGEES ADC_A..D : LDR msp (JP16-19 FERMES) ou sondes sol n3pp (JP OUVERTS). ADC_E = HumidSol msp / Luminosite n3pp / LDR ffp5cs (JP20). Pluie msp = net US1 ; DHT ext msp = net US2 (pull-up R47 si JP21 FERME) — roles disjoints.

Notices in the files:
parts and their libraries:
Diode double empreinte : DO-35 traversant pas 7,62 mm (BAT85/BAT42/BAT43) OU SOD-123 CMS (BAT43W/BAT54) ; un seul posé. Derive de D_DO-35_SOD27_P7.62mm_Horizontal et D_SOD-123 (kicad-footprints, CC-BY-SA 4.0)
